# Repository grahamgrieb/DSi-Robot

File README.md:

#### This project uses a Nintendo DSi to control a worm-like origami robot. The  DSi also streams live video data from its webcam to a TFT Display on the robot. This project involved programming custom homebrew, designing a PCB cartridge for the DSi, wireless ESP to ESP communication, image encoding, and motor control. Both the robot and DSi operate completely wirelessly.
| *The robot and the DSi with its custom cartridge slotted in* |
|:--:|
|  |

| *Block Diagram overview of all the devices in the system* |
|:--:|
|  |

The first part of this project is the Nintendo DSi. The DSi is running handwritten homebrew code (can be found in the **ds-app** folder). This application display the current DSi webcam data on the top screen. The user is able to place stickers over the webcam footage using the touchscreen. They are also able to switch between the front and back camera of the DSi. The webcam data is sent automatically if the user is in video mode, or whenever the user hits the A button when they are in photo mode. 

| *DSi Application with all the Stickers Placed* |
|:--:|
|  |

This application takes advantage of the two CPU's on the DSi. The image data is sent out over the SPI lines in the cartridge slot. The ARM9 CPU takes care of the main application, while the ARM7 CPU sends the SPI data in the background. These CPU's communicate with each other using the IPC register.

| *Close up of custom DSi Cartridge PCB and screenshots of Gerber files.* |
|:--:|
|     |

The raw bitmap image data is received over SPI on the ESP32-S3 on our custom cartridge PCB. This ESP32 is setup as SPI peripheral. It encodes the image as a JPEG (to reduce its size) and then sends it out over a WiFi WebSocket. It also receives and sends out the movement cortol signals for the robot. The code for this section can be found in **esp32-sender** folder.

The 7" TFT DIS08070H TFT Display is also powered by an ESP32-S3. The display ESP32 receives the data from the cartridge ESP32 over the direct Wifi connection. When it receives image data, it immediately draws it to the display. When it receives movement control signals, its uses our H-Bridge to appropiately tell the motors how to move. The code for this section can be found in **esp32-receiver** folder.

| *Side View of Robot* |
|:--:|
|  |

 For the robot, the design was inspired by a metamaterial soft snake robot built by the University of Southern Denmark. This design uses a Yoshimura Crease Pattern. 

The files for the cartridge PCB can be found in the **cartridge_pcb** folder and the CAD files for the cartridge housing in the **cartridge_cad** folder. The laser cutting and CAD files for the worm robot can be found in the **robot** folder.

| *Flowchart of the software/algorithm design* |
|:--:|
|  |

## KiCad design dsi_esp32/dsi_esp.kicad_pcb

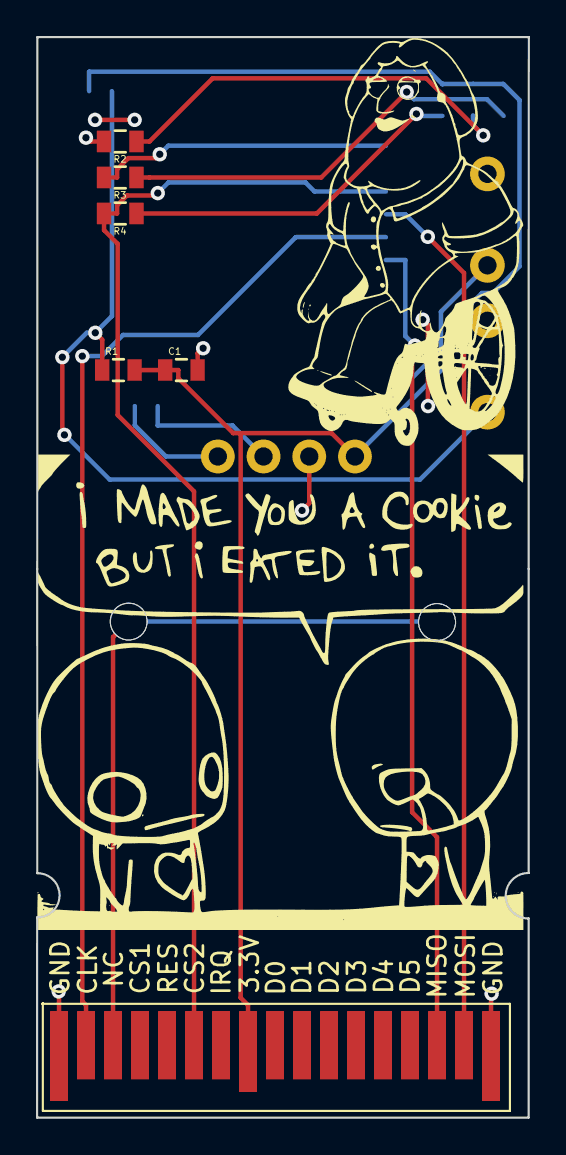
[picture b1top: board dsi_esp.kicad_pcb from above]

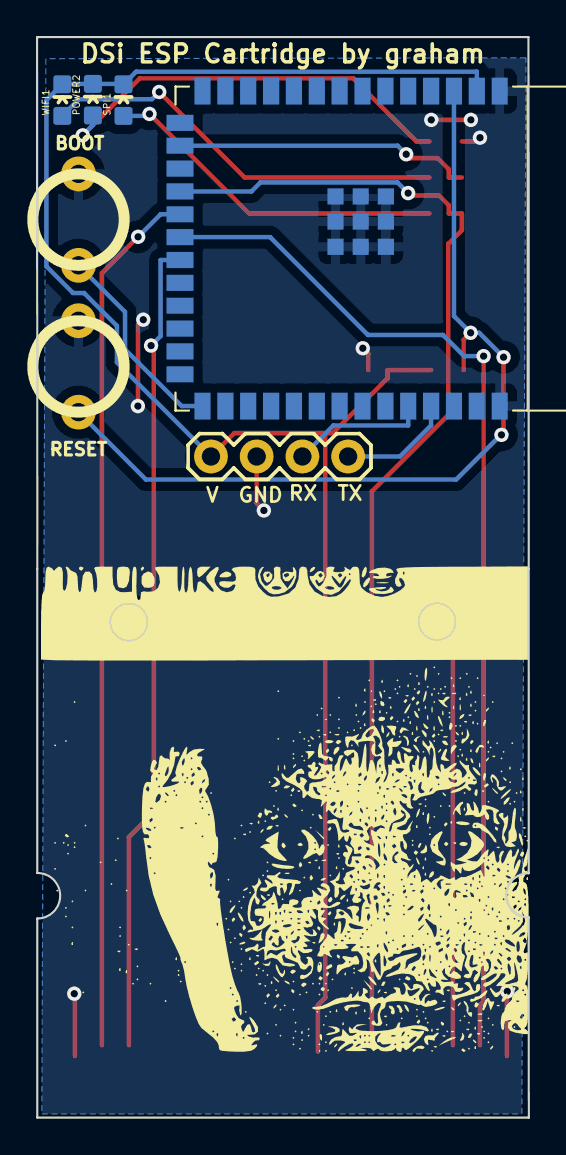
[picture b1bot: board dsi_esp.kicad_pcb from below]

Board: 2 copper layers, 27.3 x 60.0 mm, 16 parts (8 on the bottom side), 14 nets.

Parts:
BOOT1: BTN_2
C1: 0805
J1: 1X04
POWER2: RED; LED-0603
R1: 10000; 0805
R2, R3, R4: 330; 0805
RESET1: BTN_2
SPI1: GREEN; LED-0603
U1: ndsPADS; nds_contact_pads
U2: ESP32-S3-WROOM-1
WIFI1: BLUE; LED-0603
cookie: LOGO
joe: LOGO
up: LOGO

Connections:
/GND: BOOT1.P$2 (2), C1.2, J1.2, R2.2, RESET1.P$2 (2), U1.1 (GND), U1.17 (GND), U2.1 (GND), U2.40 (GND), U2.41 (GND)
/RXD: J1.3, U2.36 (U0RXD/GPIO44/CLK_OUT2)
/SPI_CLK: U1.2 (CLK), U2.20 (GPIO12/TOUCH12/ADC2_CH1/FSPICLK/FSPIIO6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)
/SPI_CS: R4.2, U1.6 (CS2_EEPROM), U2.18 (GPIO10/TOUCH10/ADC1_CH9/FSPICS0/FSPIIO4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)
/SPI_MISO: U1.15 (D6), U2.21 (GPIO13/TOUCH13/ADC2_CH2/FSPIQ/FSPIIO7/S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)
/SPI_MOSI: U1.16 (D7), U2.19 (GPIO11/TOUCH11/ADC2_CH0/FSPID/FSPIIO5/S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)
/TXD: J1.4, U2.37 (U0TXD/GPIO43/CLK_OUT1)
/VCC: C1.1, J1.1, POWER2.C, R1.2, SPI1.C, U1.8 (3.3V), U2.2 (3V3), WIFI1.C
/WIFI_IND: R3.2, U2.16 (GPIO46)
unnamed: BOOT1.P$1 (1), U2.27 (GPIO0/BOOT)
unnamed: POWER2.A, R2.1
unnamed: R3.1, WIFI1.A
unnamed: R4.1, SPI1.A
unnamed: R1.1, RESET1.P$1 (1), U2.3 (EN)

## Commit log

2024-04-04 yeetopia
2024-04-23 kicad files
2024-04-24 breakout
2024-05-01 display test
2024-05-02 fixed files
2024-05-02 added ds app
2024-05-06 got display data sending over spi
2024-05-07 vram c to vram d to fix bottom screen glitch
2024-05-07 initial bitmap code for display
2024-05-07 succesfully got bmp on display
2024-05-07 got ds bmp working
2024-05-10 ds changes
2024-05-11 flex coil
2024-05-15 added in bunch of updates for esp32 receiver and sender
2024-05-15 got rid of stuff
2024-05-17 changed ds code to send 16 bit bitmap instead of 24 and also got sender and receive code working
2024-05-20 added dsi esp32 pcb
2024-06-01 ds app updates: started using arm7 cpu to send spi messages so that rest of app doesn't freeze during send
2024-06-02 working prototype that sends the images automatically over esp-now and is able to display. esp-now is too slow however so we need to switch from it
2024-06-03 dsdasdkan
2024-06-03 dsajdlk
2024-06-04 updated sender and receiver
2024-06-05 Insanely large amount of updates: switched to websockets to greatly improve fps, added new stickers, improvements in all parts of the project
2024-06-05 added motor control logic
2024-06-05 added stop
2024-06-05 move funcs
2024-06-09 making code prettier
2024-06-18 added a bunch of comments to ds code
2024-06-18 added more comments to ESP code
2024-06-18 separated cad and pcb folders
2024-06-19 added pictures
2024-06-19 more readme additions
2024-06-19 more readme
2024-06-19 readme additions
2024-06-26 readme fixes
2024-08-08 better pics
